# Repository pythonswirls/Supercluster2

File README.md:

https://m.youtube.com/watch?v=HRfbQJ6FdF0

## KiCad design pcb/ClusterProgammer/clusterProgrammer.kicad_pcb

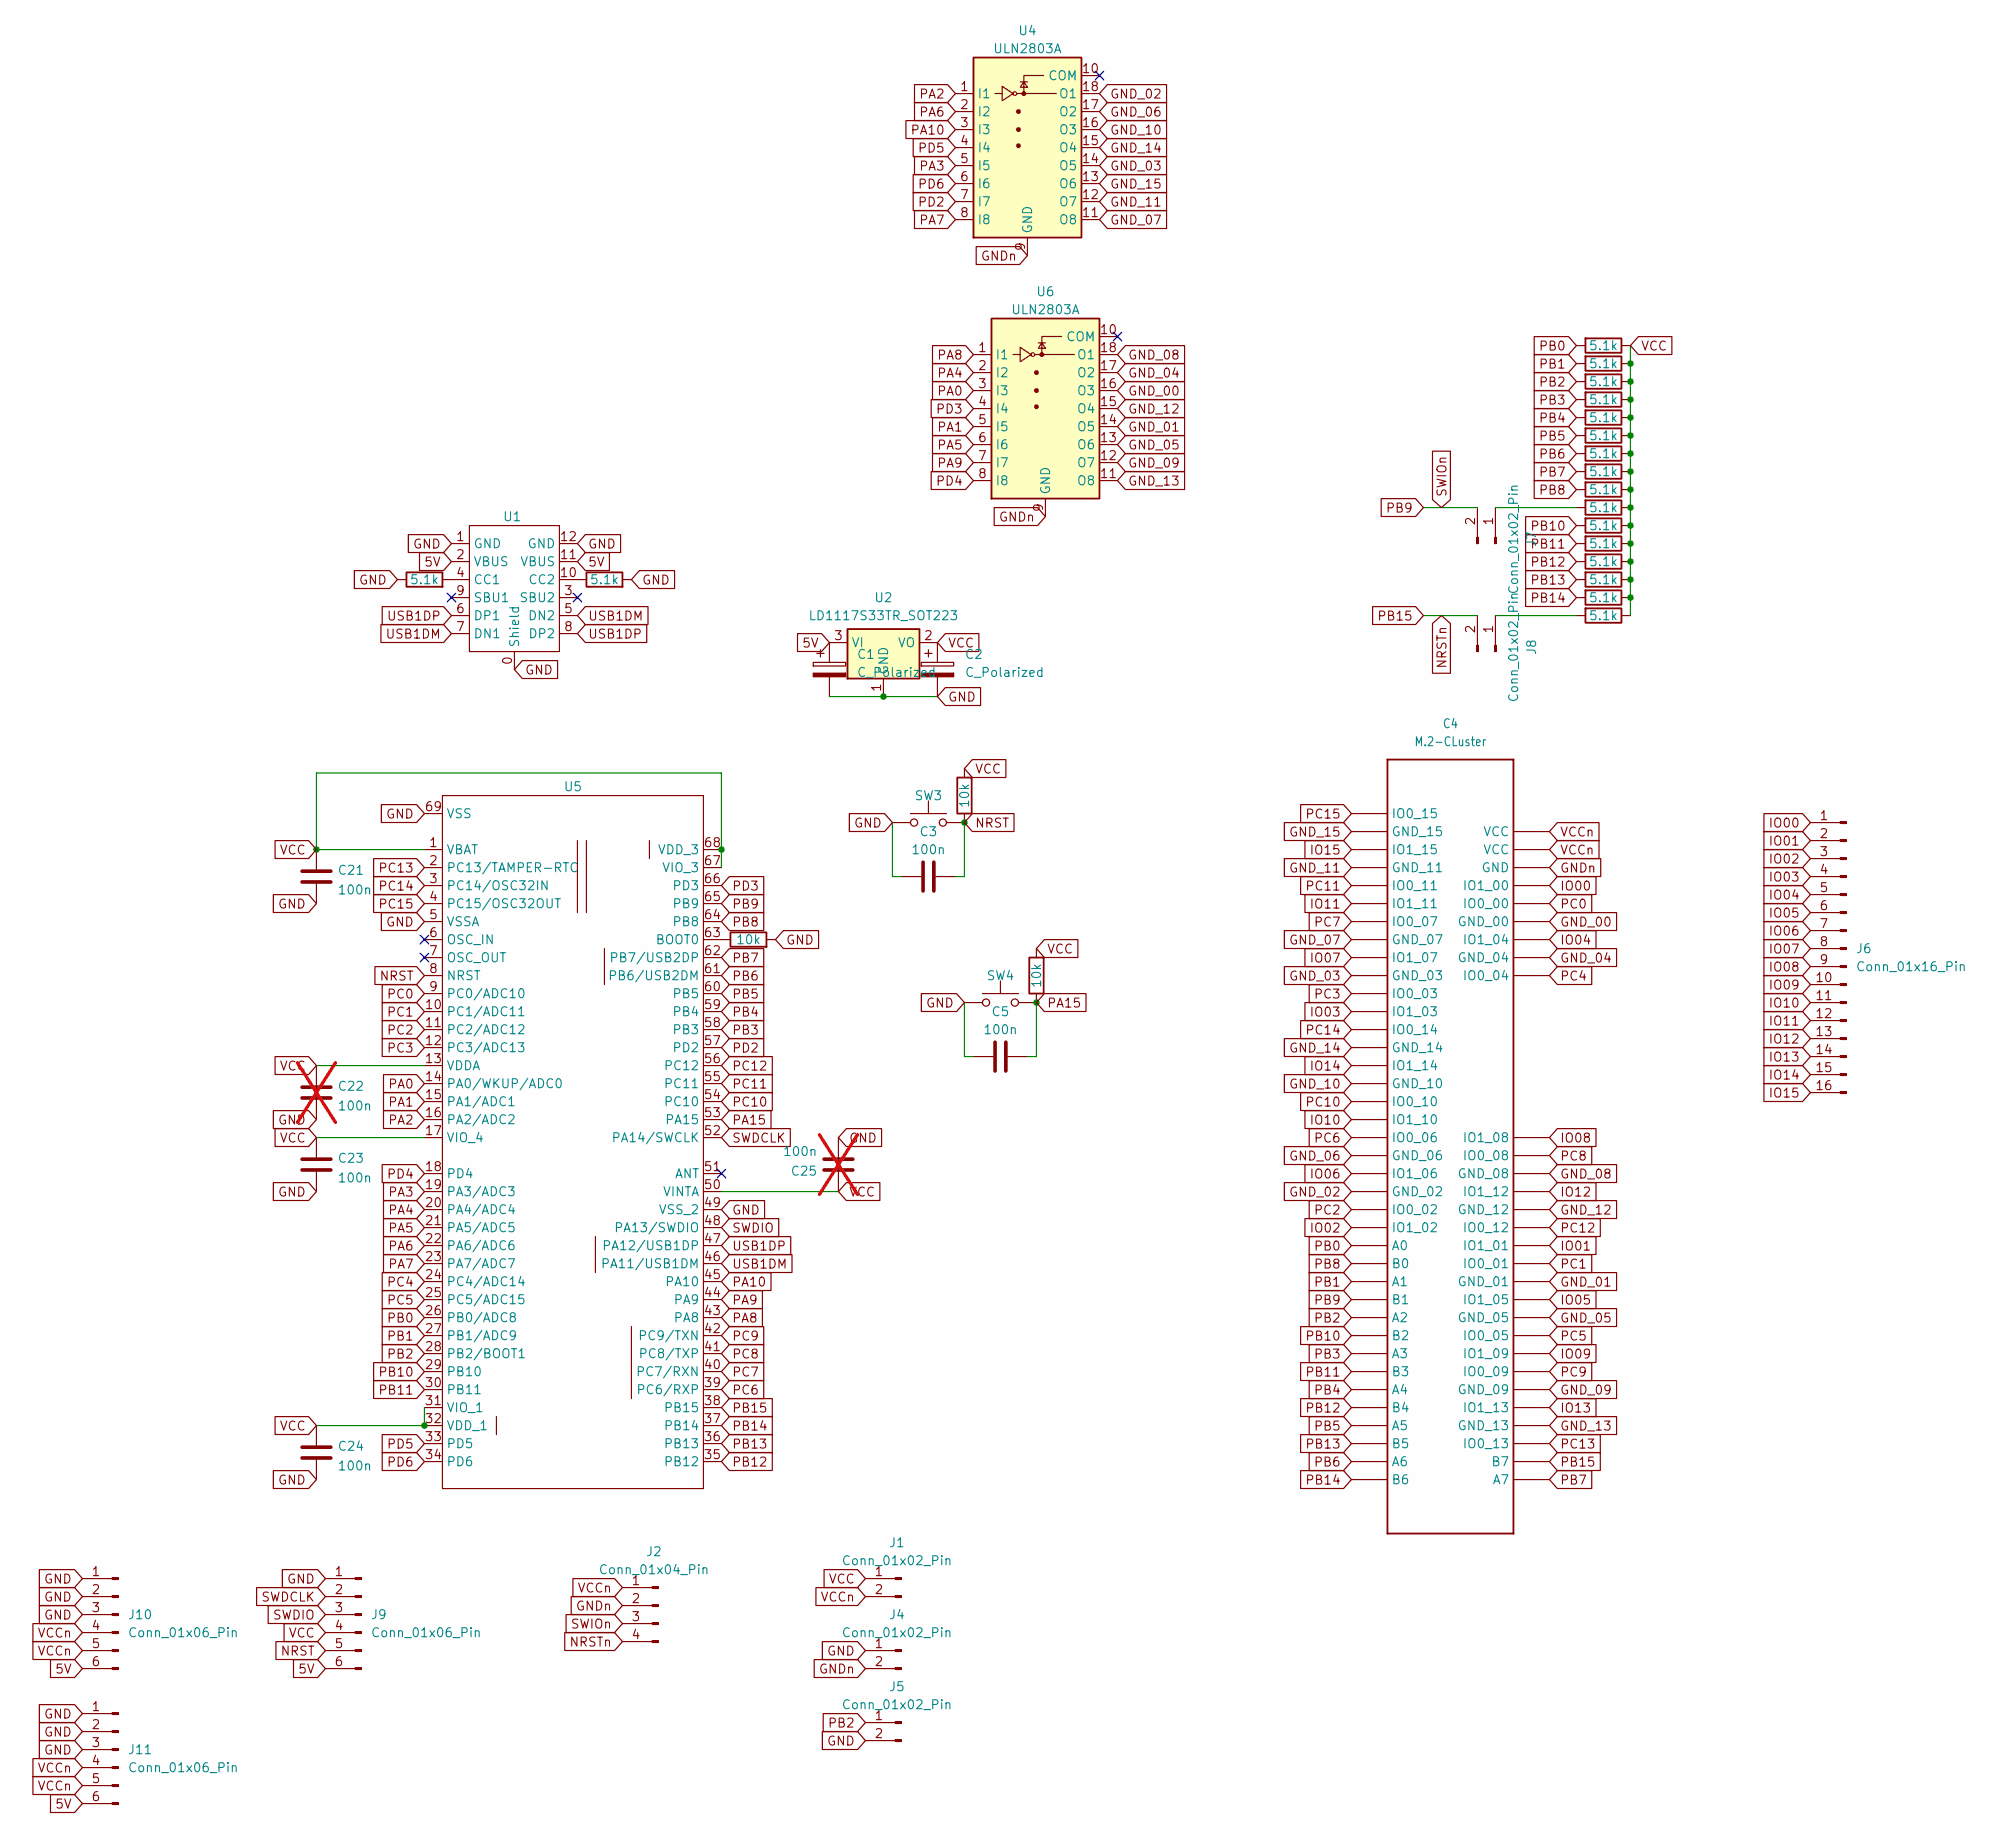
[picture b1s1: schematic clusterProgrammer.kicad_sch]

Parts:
C1, C2: C_Polarized; CP_Elec_4x4.5
C3, C5, C21, C23, C24: 100n; C_0603_1608Metric
C4: M.2-CLuster; M.2-Vertical
C22, C25: 100n; C_0603_1608Metric; not fitted
J1, J4, J5, J7, J8: Conn_01x02_Pin; PinHeader_1x02_P2.54mm_Vertical
J2: Conn_01x04_Pin; PinHeader_1x04_P2.54mm_Vertical
J6: Conn_01x16_Pin; PinSocket_1x16_P2.54mm_Vertical
J9, J10, J11: Conn_01x06_Pin; PinHeader_1x06_P2.54mm_Vertical
R1, R3, R4, R5, R6, R7, R8, R9, R10, R11, R12, R13, R14, R15, R16, R17, R18, R23: 5.1k; R_0603_1608Metric; LCSC C25905
R20, R21, R22: 10k; R_0603_1608Metric; LCSC C25905
SW3, SW4: miniButton; ButtonSMD5.2x5.2; LCSC C3020033
U1: USB-C; LCSC C165948
U2: LD1117S33TR_SOT223; SOT-223-3_TabPin2
U4, U6: ULN2803A; SOIC-18W_7.5x11.6mm_P1.27mm; LCSC C2828557
U5: QFN-68-1EP_8x8mm_P0.4mm_EP4x4mm; LCSC C5187528

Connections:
5V: C1.1, J9.6, J10.6, J11.6, U1.2 (VBUS), U1.11 (VBUS), U2.3 (VI)
GND: C1.2, C2.2, C3.2, C5.2, C21.2, C22.2, C23.2, C24.2, C25.2, J4.1, J5.2, J9.1, J10.1, J10.2, J10.3, J11.1, J11.2, J11.3, R1.1, R3.2, R20.2, SW3.1, SW4.1, U1.0 (Shield), U1.1 (GND), U1.12 (GND), U2.1 (GND), U5.5 (VSSA), U5.49 (VSS_2), U5.69 (VSS)
GND_00: C4.70 (GND_00), U6.16 (O3)
GND_01: C4.50 (GND_01), U6.14 (O5)
GND_02: C4.22 (GND_02), U4.18 (O1)
GND_03: C4.10 (GND_03), U4.14 (O5)
GND_04: C4.68 (GND_04), U6.17 (O2)
GND_05: C4.48 (GND_05), U6.13 (O6)
GND_06: C4.20 (GND_06), U4.17 (O2)
GND_07: C4.8 (GND_07), U4.11 (O8)
GND_08: C4.56 (GND_08), U6.18 (O1)
GND_09: C4.44 (GND_09), U6.12 (O7)
GND_10: C4.16 (GND_10), U4.16 (O3)
GND_11: C4.4 (GND_11), U4.12 (O7)
GND_12: C4.54 (GND_12), U6.15 (O4)
GND_13: C4.42 (GND_13), U6.11 (O8)
GND_14: C4.14 (GND_14), U4.15 (O4)
GND_15: C4.2 (GND_15), U4.13 (O6)
GNDn: C4.73 (GND), J2.2, J4.2, U4.9 (GND), U6.9 (GND)
IO00: C4.72 (IO1_00), J6.1
IO01: C4.52 (IO1_01), J6.2
IO02: C4.24 (IO1_02), J6.3
IO03: C4.12 (IO1_03), J6.4
IO04: C4.69 (IO1_04), J6.5
IO05: C4.49 (IO1_05), J6.6
IO06: C4.21 (IO1_06), J6.7
IO07: C4.9 (IO1_07), J6.8
IO08: C4.58 (IO1_08), J6.9
IO09: C4.46 (IO1_09), J6.10
IO10: C4.18 (IO1_10), J6.11
IO11: C4.6 (IO1_11), J6.12
IO12: C4.55 (IO1_12), J6.13
IO13: C4.43 (IO1_13), J6.14
IO14: C4.15 (IO1_14), J6.15
IO15: C4.3 (IO1_15), J6.16
NRST: C3.1, J9.5, R21.1, SW3.2, U5.8 (NRST)
NRSTn: C4.40 (B7), J2.4, J8.2, U5.38 (PB15)
unnamed: J7.1, R13.2
unnamed: J8.1, R23.2
unnamed: R1.2, U1.4 (CC1)
unnamed: R3.1, U1.10 (CC2)
unnamed: R20.1, U5.63 (BOOT0)
PA0: U5.14 (PA0/WKUP/ADC0), U6.3 (I3)
PA1: U5.15 (PA1/ADC1), U6.5 (I5)
PA2: U4.1 (I1), U5.16 (PA2/ADC2)
PA3: U4.5 (I5), U5.19 (PA3/ADC3)
PA4: U5.20 (PA4/ADC4), U6.2 (I2)
PA5: U5.21 (PA5/ADC5), U6.6 (I6)
PA6: U4.2 (I2), U5.22 (PA6/ADC6)
PA7: U4.8 (I8), U5.23 (PA7/ADC7)
PA8: U5.43 (PA8), U6.1 (I1)
PA9: U5.44 (PA9), U6.7 (I7)
PA10: U4.3 (I3), U5.45 (PA10)
PA15: C5.1, R22.1, SW4.2, U5.53 (PA15)
PB0: C4.25 (A0), R7.2, U5.26 (PB0/ADC8)
PB1: C4.27 (A1), R6.2, U5.27 (PB1/ADC9)
PB2: C4.29 (A2), J5.1, R5.2, U5.28 (PB2/BOOT1)
PB3: C4.31 (A3), R4.2, U5.58 (PB3)
PB4: C4.33 (A4), R8.2, U5.59 (PB4)
PB5: C4.35 (A5), R9.2, U5.60 (PB5)
PB6: C4.37 (A6), R10.2, U5.61 (PB6/USB2DM)
PB7: C4.39 (A7), R11.2, U5.62 (PB7/USB2DP)
PB8: C4.26 (B0), R12.2, U5.64 (PB8)
PB9: C4.28 (B1), J2.3, J7.2, U5.65 (PB9)
PB10: C4.30 (B2), R14.2, U5.29 (PB10)
PB11: C4.32 (B3), R15.2, U5.30 (PB11)
PB12: C4.34 (B4), R16.2, U5.35 (PB12)
PB13: C4.36 (B5), R17.2, U5.36 (PB13)
PB14: C4.38 (B6), R18.2, U5.37 (PB14)
PC0: C4.71 (IO0_00), U5.9 (PC0/ADC10)
PC1: C4.51 (IO0_01), U5.10 (PC1/ADC11)
PC2: C4.23 (IO0_02), U5.11 (PC2/ADC12)
PC3: C4.11 (IO0_03), U5.12 (PC3/ADC13)
PC4: C4.67 (IO0_04), U5.24 (PC4/ADC14)
PC5: C4.47 (IO0_05), U5.25 (PC5/ADC15)
PC6: C4.19 (IO0_06), U5.39 (PC6/RXP)
PC7: C4.7 (IO0_07), U5.40 (PC7/RXN)
PC8: C4.57 (IO0_08), U5.41 (PC8/TXP)
PC9: C4.45 (IO0_09), U5.42 (PC9/TXN)
PC10: C4.17 (IO0_10), U5.54 (PC10)
PC11: C4.5 (IO0_11), U5.55 (PC11)
PC12: C4.53 (IO0_12), U5.56 (PC12)
PC13: C4.41 (IO0_13), U5.2 (PC13/TAMPER-RTC)
PC14: C4.13 (IO0_14), U5.3 (PC14/OSC32IN)
PC15: C4.1 (IO0_15), U5.4 (PC15/OSC32OUT)
PD2: U4.7 (I7), U5.57 (PD2)
PD3: U5.66 (PD3), U6.4 (I4)
PD4: U5.18 (PD4), U6.8 (I8)
PD5: U4.4 (I4), U5.33 (PD5)
PD6: U4.6 (I6), U5.34 (PD6)
SWDCLK: J9.2, U5.52 (PA14/SWCLK)
SWDIO: J9.3, U5.48 (PA13/SWDIO)
USB1DM: U1.5 (DN2), U1.7 (DN1), U5.46 (PA11/USB1DM)
USB1DP: U1.6 (DP1), U1.8 (DP2), U5.47 (PA12/USB1DP)
VCC: C2.1, C21.1, C22.1, C23.1, C24.1, C25.1, J1.1, J9.4, R4.1, R5.1, R6.1, R7.1, R8.1, R9.1, R10.1, R11.1, R12.1, R13.1, R14.1, R15.1, R16.1, R17.1, R18.1, R21.2, R22.2, R23.1, U2.2 (VO), U5.1 (VBAT), U5.13 (VDDA), U5.17 (VIO_4), U5.31 (VIO_1), U5.32 (VDD_1), U5.50 (VINTA), U5.67 (VIO_3), U5.68 (VDD_3)
VCCn: C4.74 (VCC), C4.75 (VCC), J1.2, J2.1, J10.4, J10.5, J11.4, J11.5

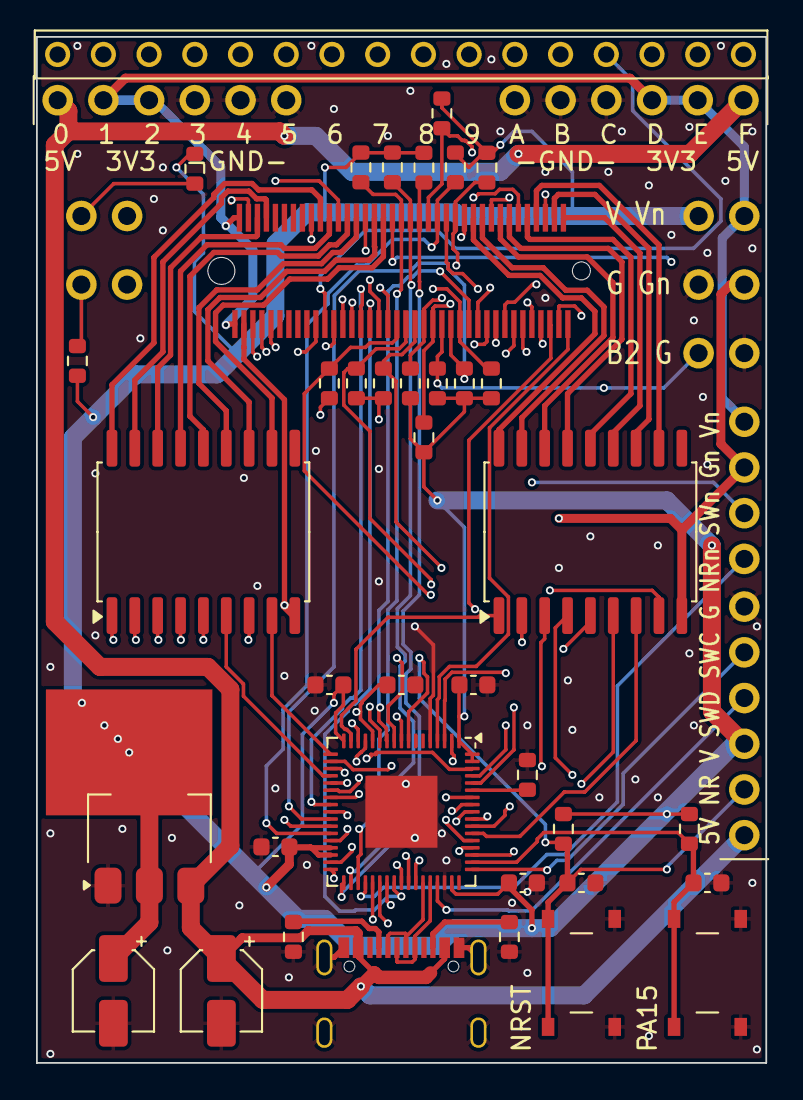
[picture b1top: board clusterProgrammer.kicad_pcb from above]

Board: 4 copper layers, 40.5 x 57.0 mm, 48 parts (0 on the bottom side), 96 nets.

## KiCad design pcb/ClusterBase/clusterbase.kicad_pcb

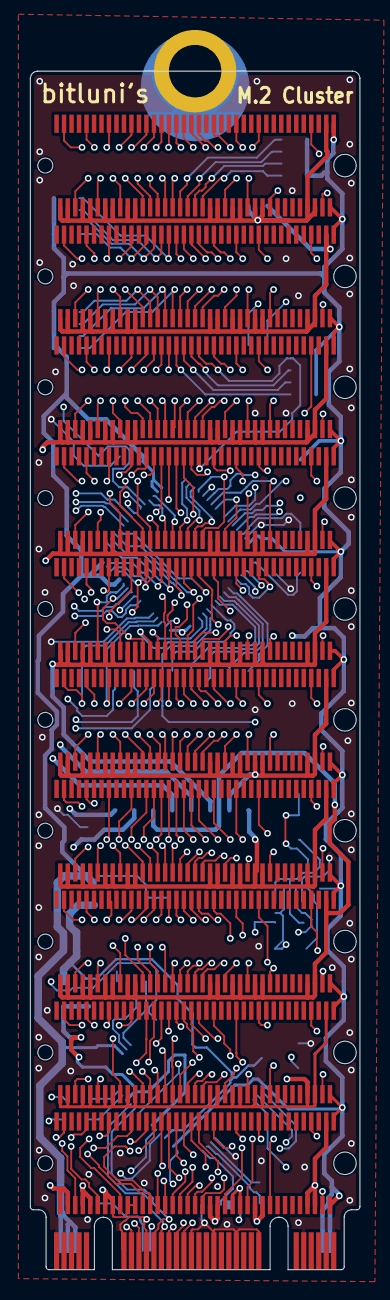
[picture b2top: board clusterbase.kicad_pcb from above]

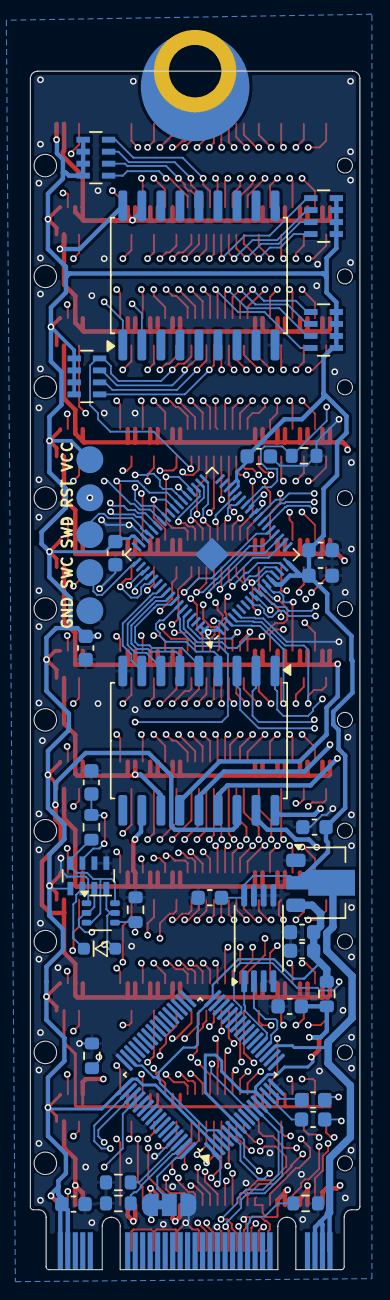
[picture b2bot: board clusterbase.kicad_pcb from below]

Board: 4 copper layers, 22.0 x 80.0 mm, 48 parts (37 on the bottom side), 82 nets.

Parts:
C1, C2, C3, C10, C12, C15, C26, C27, C28, C29, C30, C31: 100n; C_0603_1608Metric
C5, C6, C7, C9, C13, C14, C18, C19, C20, C21: M.2-CLuster; M.2-Vertical-short Pads
C8, C11: 10u; C_0603_1608Metric
D1: D; D_SOD-323
JP2: Jumper_3_Bridged12; SolderJumper-3_P1.3mm_Bridged12_RoundedPad1.0x1.5mm
Q1: UMH3N; SOT-363_SC-70-6
R9, R10, R11: 0; R_0603_1608Metric
R12: 12k; R_0603_1608Metric
R15, R16: 100k; R_0603_1608Metric
R18, R19: 10k; R_0603_1608Metric
RN6, RN7, RN8, RN9: 1k; R_Array_Concave_4x0603
RN10: 10k; R_Array_Concave_4x0603
TP2: TestPoint; Testpoint5
U1: CH382; LQFP-64_7x7mm_P0.4mm
U2: M.2-B+M-KEY-PCIe; M.2-B+M-KEY 2280
U3: MCP1703Ax-180xxMB; SOT-89-3
U4: M24C02-FDW; TSSOP-8_4.4x3mm_P0.65mm
U5, U7: ULN2803A; SOIC-18W_7.5x11.6mm_P1.27mm
U6: QFN-68-1EP_8x8mm_P0.4mm_EP1x1mm

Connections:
1V8: C10.2, C11.2, R9.1, U1.4 (VCC18), U1.32 (VCC18), U1.47 (VCC18), U3.3 (VO)
1V8A: C12.2, R9.2, U1.7 (VCC18A), U1.13 (VCC18A)
/CKSEL: JP2.2 (C), U1.64 (CKSEL)
/CLKREQ#: R18.2, U2.P$52 (CLKREQ#)
/DTR: Q1.2 (B1), RN10.3 (R3.1), U1.52 (DTR0)
/PECK+: U1.5 (PECK+), U2.P$55 (REFCLK+)
/PECK-: U1.6 (PECK-), U2.P$53 (REFCLK-)
/PER+: U1.11 (PER+), U2.P$49 (PER0+)
/PER-: U1.12 (PER-), U2.P$47 (PER0-)
/PET+: C2.2, U1.15 (PET+)
/PET-: C1.2, U1.14 (PET-)
/RST#: JP2.1 (A), U1.1 (PERST#), U2.P$50 (PERST#)
/RST_CH32#: C26.1, R16.2, RN10.7 (R2.2), TP2.4, U6.8 (NRST)
/RTS: D1.2 (A), Q1.5 (B2), RN10.4 (R4.1), U1.51 (RTS0)
/RX: U1.27 (RXD0), U6.44 (PA9)
/TX: U1.50 (TXD0), U6.45 (PA10)
BOOT0: Q1.4 (E2), R15.1, U6.63 (BOOT0)
GND: C3.1, C8.1, C10.1, C11.1, C12.1, C15.1, C26.2, C27.2, C28.2, C29.2, C30.2, C31.2, JP2.3 (B), Q1.1 (E1), R10.2, R11.2, R12.2, R15.2, R18.1, R19.2, RN10.5 (R4.2), RN10.6 (R3.2), TP2.1, U1.3 (GND), U1.8 (GND), U1.9 (GND), U1.16 (GND), U1.33 (GND), U1.48 (GND), U1.56 (GND), U1.61 (GND), U2.P$1 (CONFIG3/GND), U2.P$3 (GND), U2.P$9 (GND), U2.P$21 (CONFIG_0/GND), U2.P$27 (GND), U2.P$33 (GND), U2.P$39 (GND), U2.P$45 (GND), U2.P$51 (GND), U2.P$57 (GND), U2.P$71 (GND), U2.P$73 (GND), U2.P$75 (CONFIG_2/GND), U3.1 (GND), U4.3 (E2), U4.4 (VSS), U4.5 (SDA), U4.6 (SCL), U4.7 (~WC), U5.9 (GND), U6.5 (VSSA), U6.49 (VSS_2), U6.69 (VSS), U7.9 (GND)
GND00: C5.2 (GND_15), C5.4 (GND_11), C5.8 (GND_07), C5.10 (GND_03), C5.14 (GND_14), C5.16 (GND_10), C5.20 (GND_06), C5.22 (GND_02), C5.42 (GND_13), C5.44 (GND_09), C5.48 (GND_05), C5.50 (GND_01), C5.54 (GND_12), C5.56 (GND_08), C5.68 (GND_04), C5.70 (GND_00), C5.73 (GND), U5.17 (O2)
GND01: C6.2 (GND_15), C6.4 (GND_11), C6.8 (GND_07), C6.10 (GND_03), C6.14 (GND_14), C6.16 (GND_10), C6.20 (GND_06), C6.22 (GND_02), C6.42 (GND_13), C6.44 (GND_09), C6.48 (GND_05), C6.50 (GND_01), C6.54 (GND_12), C6.56 (GND_08), C6.68 (GND_04), C6.70 (GND_00), C6.73 (GND), U5.18 (O1)
GND02: C7.2 (GND_15), C7.4 (GND_11), C7.8 (GND_07), C7.10 (GND_03), C7.14 (GND_14), C7.16 (GND_10), C7.20 (GND_06), C7.22 (GND_02), C7.42 (GND_13), C7.44 (GND_09), C7.48 (GND_05), C7.50 (GND_01), C7.54 (GND_12), C7.56 (GND_08), C7.68 (GND_04), C7.70 (GND_00), C7.73 (GND), U5.16 (O3)
GND03: C9.2 (GND_15), C9.4 (GND_11), C9.8 (GND_07), C9.10 (GND_03), C9.14 (GND_14), C9.16 (GND_10), C9.20 (GND_06), C9.22 (GND_02), C9.42 (GND_13), C9.44 (GND_09), C9.48 (GND_05), C9.50 (GND_01), C9.54 (GND_12), C9.56 (GND_08), C9.68 (GND_04), C9.70 (GND_00), C9.73 (GND), U5.11 (O8)
GND04: C13.2 (GND_15), C13.4 (GND_11), C13.8 (GND_07), C13.10 (GND_03), C13.14 (GND_14), C13.16 (GND_10), C13.20 (GND_06), C13.22 (GND_02), C13.42 (GND_13), C13.44 (GND_09), C13.48 (GND_05), C13.50 (GND_01), C13.54 (GND_12), C13.56 (GND_08), C13.68 (GND_04), C13.70 (GND_00), C13.73 (GND), U5.12 (O7)
GND05: C14.2 (GND_15), C14.4 (GND_11), C14.8 (GND_07), C14.10 (GND_03), C14.14 (GND_14), C14.16 (GND_10), C14.20 (GND_06), C14.22 (GND_02), C14.42 (GND_13), C14.44 (GND_09), C14.48 (GND_05), C14.50 (GND_01), C14.54 (GND_12), C14.56 (GND_08), C14.68 (GND_04), C14.70 (GND_00), C14.73 (GND), U5.13 (O6)
GND06: C18.2 (GND_15), C18.4 (GND_11), C18.8 (GND_07), C18.10 (GND_03), C18.14 (GND_14), C18.16 (GND_10), C18.20 (GND_06), C18.22 (GND_02), C18.42 (GND_13), C18.44 (GND_09), C18.48 (GND_05), C18.50 (GND_01), C18.54 (GND_12), C18.56 (GND_08), C18.68 (GND_04), C18.70 (GND_00), C18.73 (GND), U5.14 (O5)
GND07: C19.2 (GND_15), C19.4 (GND_11), C19.8 (GND_07), C19.10 (GND_03), C19.14 (GND_14), C19.16 (GND_10), C19.20 (GND_06), C19.22 (GND_02), C19.42 (GND_13), C19.44 (GND_09), C19.48 (GND_05), C19.50 (GND_01), C19.54 (GND_12), C19.56 (GND_08), C19.68 (GND_04), C19.70 (GND_00), C19.73 (GND), U5.15 (O4)
GND08: C20.2 (GND_15), C20.4 (GND_11), C20.8 (GND_07), C20.10 (GND_03), C20.14 (GND_14), C20.16 (GND_10), C20.20 (GND_06), C20.22 (GND_02), C20.42 (GND_13), C20.44 (GND_09), C20.48 (GND_05), C20.50 (GND_01), C20.54 (GND_12), C20.56 (GND_08), C20.68 (GND_04), C20.70 (GND_00), C20.73 (GND), U7.18 (O1)
GND09: C21.2 (GND_15), C21.4 (GND_11), C21.8 (GND_07), C21.10 (GND_03), C21.14 (GND_14), C21.16 (GND_10), C21.20 (GND_06), C21.22 (GND_02), C21.42 (GND_13), C21.44 (GND_09), C21.48 (GND_05), C21.50 (GND_01), C21.54 (GND_12), C21.56 (GND_08), C21.68 (GND_04), C21.70 (GND_00), C21.73 (GND), U7.17 (O2)
unnamed: D1.1 (K), RN10.2 (R2.1)
unnamed: Q1.3 (C2), Q1.6 (C1), R16.1, RN10.8 (R1.2)
unnamed: R11.1, U1.62 (MDPRT#)
unnamed: R10.1, U1.63 (MDSEL)
unnamed: R12.1, U1.10 (RREF)
unnamed: U1.20 (SCL), U4.2 (E1)
unnamed: U1.21 (SDA), U4.1 (E0)
unnamed: C2.1, U2.P$43 (PET0+)
unnamed: C1.1, U2.P$41 (PET0-)
PA0: C5.25 (A0), C6.25 (A0), C7.25 (A0), C9.25 (A0), C13.25 (A0), C14.25 (A0), C18.25 (A0), C19.25 (A0), C20.25 (A0), C21.25 (A0), RN6.4 (R4.1), U6.14 (PA0/WKUP/ADC0)
PA1: C5.27 (A1), C6.27 (A1), C7.27 (A1), C9.27 (A1), C13.27 (A1), C14.27 (A1), C18.27 (A1), C19.27 (A1), C20.27 (A1), C21.27 (A1), RN6.3 (R3.1), U6.15 (PA1/ADC1)
PA2: C5.29 (A2), C6.29 (A2), C7.29 (A2), C9.29 (A2), C13.29 (A2), C14.29 (A2), C18.29 (A2), C19.29 (A2), C20.29 (A2), C21.29 (A2), RN6.2 (R2.1), U6.16 (PA2/ADC2)
PA3: C5.31 (A3), C6.31 (A3), C7.31 (A3), C9.31 (A3), C13.31 (A3), C14.31 (A3), C18.31 (A3), C19.31 (A3), C20.31 (A3), C21.31 (A3), RN6.1 (R1.1), U6.19 (PA3/ADC3)
PA4: C5.33 (A4), C6.33 (A4), C7.33 (A4), C9.33 (A4), C13.33 (A4), C14.33 (A4), C18.33 (A4), C19.33 (A4), C20.33 (A4), C21.33 (A4), RN7.1 (R1.1), U6.20 (PA4/ADC4)
PA5: C5.35 (A5), C6.35 (A5), C7.35 (A5), C9.35 (A5), C13.35 (A5), C14.35 (A5), C18.35 (A5), C19.35 (A5), C20.35 (A5), C21.35 (A5), RN7.2 (R2.1), U6.21 (PA5/ADC5)
PA6: C5.37 (A6), C6.37 (A6), C7.37 (A6), C9.37 (A6), C13.37 (A6), C14.37 (A6), C18.37 (A6), C19.37 (A6), C20.37 (A6), C21.37 (A6), RN7.3 (R3.1), U6.22 (PA6/ADC6)
PA7: C5.39 (A7), C6.39 (A7), C7.39 (A7), C9.39 (A7), C13.39 (A7), C14.39 (A7), C18.39 (A7), C19.39 (A7), C20.39 (A7), C21.39 (A7), RN7.4 (R4.1), U6.23 (PA7/ADC7)
PA11: U6.46 (PA11/USB1DM), U7.1 (I1)
PA12: U6.47 (PA12/USB1DP), U7.2 (I2)
PA13: TP2.3, U6.48 (PA13/SWDIO)
PA14: TP2.2, U6.52 (PA14/SWCLK)
PB0: U5.2 (I2), U6.26 (PB0/ADC8)
PB1: U5.1 (I1), U6.27 (PB1/ADC9)
PB2: R19.1, U5.3 (I3), U6.28 (PB2/BOOT1)
PB3: U5.8 (I8), U6.58 (PB3)
PB4: U5.7 (I7), U6.59 (PB4)
PB5: U5.6 (I6), U6.60 (PB5)
PB6: U5.5 (I5), U6.61 (PB6/USB2DM)
PB7: U5.4 (I4), U6.62 (PB7/USB2DP)
PB8: C5.26 (B0), C6.26 (B0), C7.26 (B0), C9.26 (B0), C13.26 (B0), C14.26 (B0), C18.26 (B0), C19.26 (B0), C20.26 (B0), C21.26 (B0), RN8.1 (R1.1), U6.64 (PB8)
PB9: C5.28 (B1), C6.28 (B1), C7.28 (B1), C9.28 (B1), C13.28 (B1), C14.28 (B1), C18.28 (B1), C19.28 (B1), C20.28 (B1), C21.28 (B1), RN8.2 (R2.1), U6.65 (PB9)
PB10: C5.30 (B2), C6.30 (B2), C7.30 (B2), C9.30 (B2), C13.30 (B2), C14.30 (B2), C18.30 (B2), C19.30 (B2), C20.30 (B2), C21.30 (B2), RN8.3 (R3.1), U6.29 (PB10)
PB11: C5.32 (B3), C6.32 (B3), C7.32 (B3), C9.32 (B3), C13.32 (B3), C14.32 (B3), C18.32 (B3), C19.32 (B3), C20.32 (B3), C21.32 (B3), RN8.4 (R4.1), U6.30 (PB11)
PB12: C5.34 (B4), C6.34 (B4), C7.34 (B4), C9.34 (B4), C13.34 (B4), C14.34 (B4), C18.34 (B4), C19.34 (B4), C20.34 (B4), C21.34 (B4), RN9.4 (R4.1), U6.35 (PB12)
PB13: C5.36 (B5), C6.36 (B5), C7.36 (B5), C9.36 (B5), C13.36 (B5), C14.36 (B5), C18.36 (B5), C19.36 (B5), C20.36 (B5), C21.36 (B5), RN9.3 (R3.1), U6.36 (PB13)
PB14: C5.38 (B6), C6.38 (B6), C7.38 (B6), C9.38 (B6), C13.38 (B6), C14.38 (B6), C18.38 (B6), C19.38 (B6), C20.38 (B6), C21.38 (B6), RN9.2 (R2.1), U6.37 (PB14)
PB15: C5.40 (B7), C6.40 (B7), C7.40 (B7), C9.40 (B7), C13.40 (B7), C14.40 (B7), C18.40 (B7), C19.40 (B7), C20.40 (B7), C21.40 (B7), RN9.1 (R1.1), U6.38 (PB15)
PC0: C5.72 (IO1_00), C6.72 (IO1_00), C7.72 (IO1_00), C9.72 (IO1_00), C13.72 (IO1_00), C14.72 (IO1_00), C18.72 (IO1_00), C19.72 (IO1_00), C20.72 (IO1_00), C21.72 (IO1_00), U6.9 (PC0/ADC10)
PC1: C5.52 (IO1_01), C6.52 (IO1_01), C7.52 (IO1_01), C9.52 (IO1_01), C13.52 (IO1_01), C14.52 (IO1_01), C18.52 (IO1_01), C19.52 (IO1_01), C20.52 (IO1_01), C21.52 (IO1_01), U6.10 (PC1/ADC11)
PC2: C5.24 (IO1_02), C6.24 (IO1_02), C7.24 (IO1_02), C9.24 (IO1_02), C13.24 (IO1_02), C14.24 (IO1_02), C18.24 (IO1_02), C19.24 (IO1_02), C20.24 (IO1_02), C21.24 (IO1_02), U6.11 (PC2/ADC12)
PC3: C5.12 (IO1_03), C6.12 (IO1_03), C7.12 (IO1_03), C9.12 (IO1_03), C13.12 (IO1_03), C14.12 (IO1_03), C18.12 (IO1_03), C19.12 (IO1_03), C20.12 (IO1_03), C21.12 (IO1_03), U6.12 (PC3/ADC13)
PC4: C5.69 (IO1_04), C6.69 (IO1_04), C7.69 (IO1_04), C9.69 (IO1_04), C13.69 (IO1_04), C14.69 (IO1_04), C18.69 (IO1_04), C19.69 (IO1_04), C20.69 (IO1_04), C21.69 (IO1_04), U6.24 (PC4/ADC14)
PC5: C5.49 (IO1_05), C6.49 (IO1_05), C7.49 (IO1_05), C9.49 (IO1_05), C13.49 (IO1_05), C14.49 (IO1_05), C18.49 (IO1_05), C19.49 (IO1_05), C20.49 (IO1_05), C21.49 (IO1_05), U6.25 (PC5/ADC15)
PC6: C5.21 (IO1_06), C6.21 (IO1_06), C7.21 (IO1_06), C9.21 (IO1_06), C13.21 (IO1_06), C14.21 (IO1_06), C18.21 (IO1_06), C19.21 (IO1_06), C20.21 (IO1_06), C21.21 (IO1_06), U6.39 (PC6/RXP)
PC7: C5.9 (IO1_07), C6.9 (IO1_07), C7.9 (IO1_07), C9.9 (IO1_07), C13.9 (IO1_07), C14.9 (IO1_07), C18.9 (IO1_07), C19.9 (IO1_07), C20.9 (IO1_07), C21.9 (IO1_07), U6.40 (PC7/RXN)
PC8: C5.58 (IO1_08), C6.58 (IO1_08), C7.58 (IO1_08), C9.58 (IO1_08), C13.58 (IO1_08), C14.58 (IO1_08), C18.58 (IO1_08), C19.58 (IO1_08), C20.58 (IO1_08), C21.58 (IO1_08), U6.41 (PC8/TXP)
PC9: C5.46 (IO1_09), C6.46 (IO1_09), C7.46 (IO1_09), C9.46 (IO1_09), C13.46 (IO1_09), C14.46 (IO1_09), C18.46 (IO1_09), C19.46 (IO1_09), C20.46 (IO1_09), C21.46 (IO1_09), U6.42 (PC9/TXN)
PC10: C5.18 (IO1_10), C6.18 (IO1_10), C7.18 (IO1_10), C9.18 (IO1_10), C13.18 (IO1_10), C14.18 (IO1_10), C18.18 (IO1_10), C19.18 (IO1_10), C20.18 (IO1_10), C21.18 (IO1_10), U6.54 (PC10)
PC11: C5.6 (IO1_11), C6.6 (IO1_11), C7.6 (IO1_11), C9.6 (IO1_11), C13.6 (IO1_11), C14.6 (IO1_11), C18.6 (IO1_11), C19.6 (IO1_11), C20.6 (IO1_11), C21.6 (IO1_11), U6.55 (PC11)
PC12: C5.55 (IO1_12), C6.55 (IO1_12), C7.55 (IO1_12), C9.55 (IO1_12), C13.55 (IO1_12), C14.55 (IO1_12), C18.55 (IO1_12), C19.55 (IO1_12), C20.55 (IO1_12), C21.55 (IO1_12), U6.56 (PC12)
PC13: C5.43 (IO1_13), C6.43 (IO1_13), C7.43 (IO1_13), C9.43 (IO1_13), C13.43 (IO1_13), C14.43 (IO1_13), C18.43 (IO1_13), C19.43 (IO1_13), C20.43 (IO1_13), C21.43 (IO1_13), U6.2 (PC13/TAMPER-RTC)
PC14: C5.15 (IO1_14), C6.15 (IO1_14), C7.15 (IO1_14), C9.15 (IO1_14), C13.15 (IO1_14), C14.15 (IO1_14), C18.15 (IO1_14), C19.15 (IO1_14), C20.15 (IO1_14), C21.15 (IO1_14), U6.3 (PC14/OSC32IN)
PC15: C5.3 (IO1_15), C6.3 (IO1_15), C7.3 (IO1_15), C9.3 (IO1_15), C13.3 (IO1_15), C14.3 (IO1_15), C18.3 (IO1_15), C19.3 (IO1_15), C20.3 (IO1_15), C21.3 (IO1_15), U6.4 (PC15/OSC32OUT)
VCC: C3.2, C5.74 (VCC), C5.75 (VCC), C6.74 (VCC), C6.75 (VCC), C7.74 (VCC), C7.75 (VCC), C8.2, C9.74 (VCC), C9.75 (VCC), C13.74 (VCC), C13.75 (VCC), C14.74 (VCC), C14.75 (VCC), C15.2, C18.74 (VCC), C18.75 (VCC), C19.74 (VCC), C19.75 (VCC), C20.74 (VCC), C20.75 (VCC), C21.74 (VCC), C21.75 (VCC), C27.1, C28.1, C29.1, C30.1, C31.1, RN6.5 (R4.2), RN6.6 (R3.2), RN6.7 (R2.2), RN6.8 (R1.2), RN7.5 (R4.2), RN7.6 (R3.2), RN7.7 (R2.2), RN7.8 (R1.2), RN8.5 (R4.2), RN8.6 (R3.2), RN8.7 (R2.2), RN8.8 (R1.2), RN9.5 (R4.2), RN9.6 (R3.2), RN9.7 (R2.2), RN9.8 (R1.2), RN10.1 (R1.1), TP2.5, U1.2 (VCC33), U1.19 (VCC33), U1.49 (VCC33), U2.P$2 (3V3), U2.P$4 (3V3), U2.P$70 (3V3), U2.P$72 (3V3), U2.P$74 (3V3), U3.2 (VI), U4.8 (VCC), U6.1 (VBAT), U6.13 (VDDA), U6.17 (VIO_4), U6.31 (VIO_1), U6.32 (VDD_1), U6.50 (VINTA), U6.67 (VIO_3), U6.68 (VDD_3)
